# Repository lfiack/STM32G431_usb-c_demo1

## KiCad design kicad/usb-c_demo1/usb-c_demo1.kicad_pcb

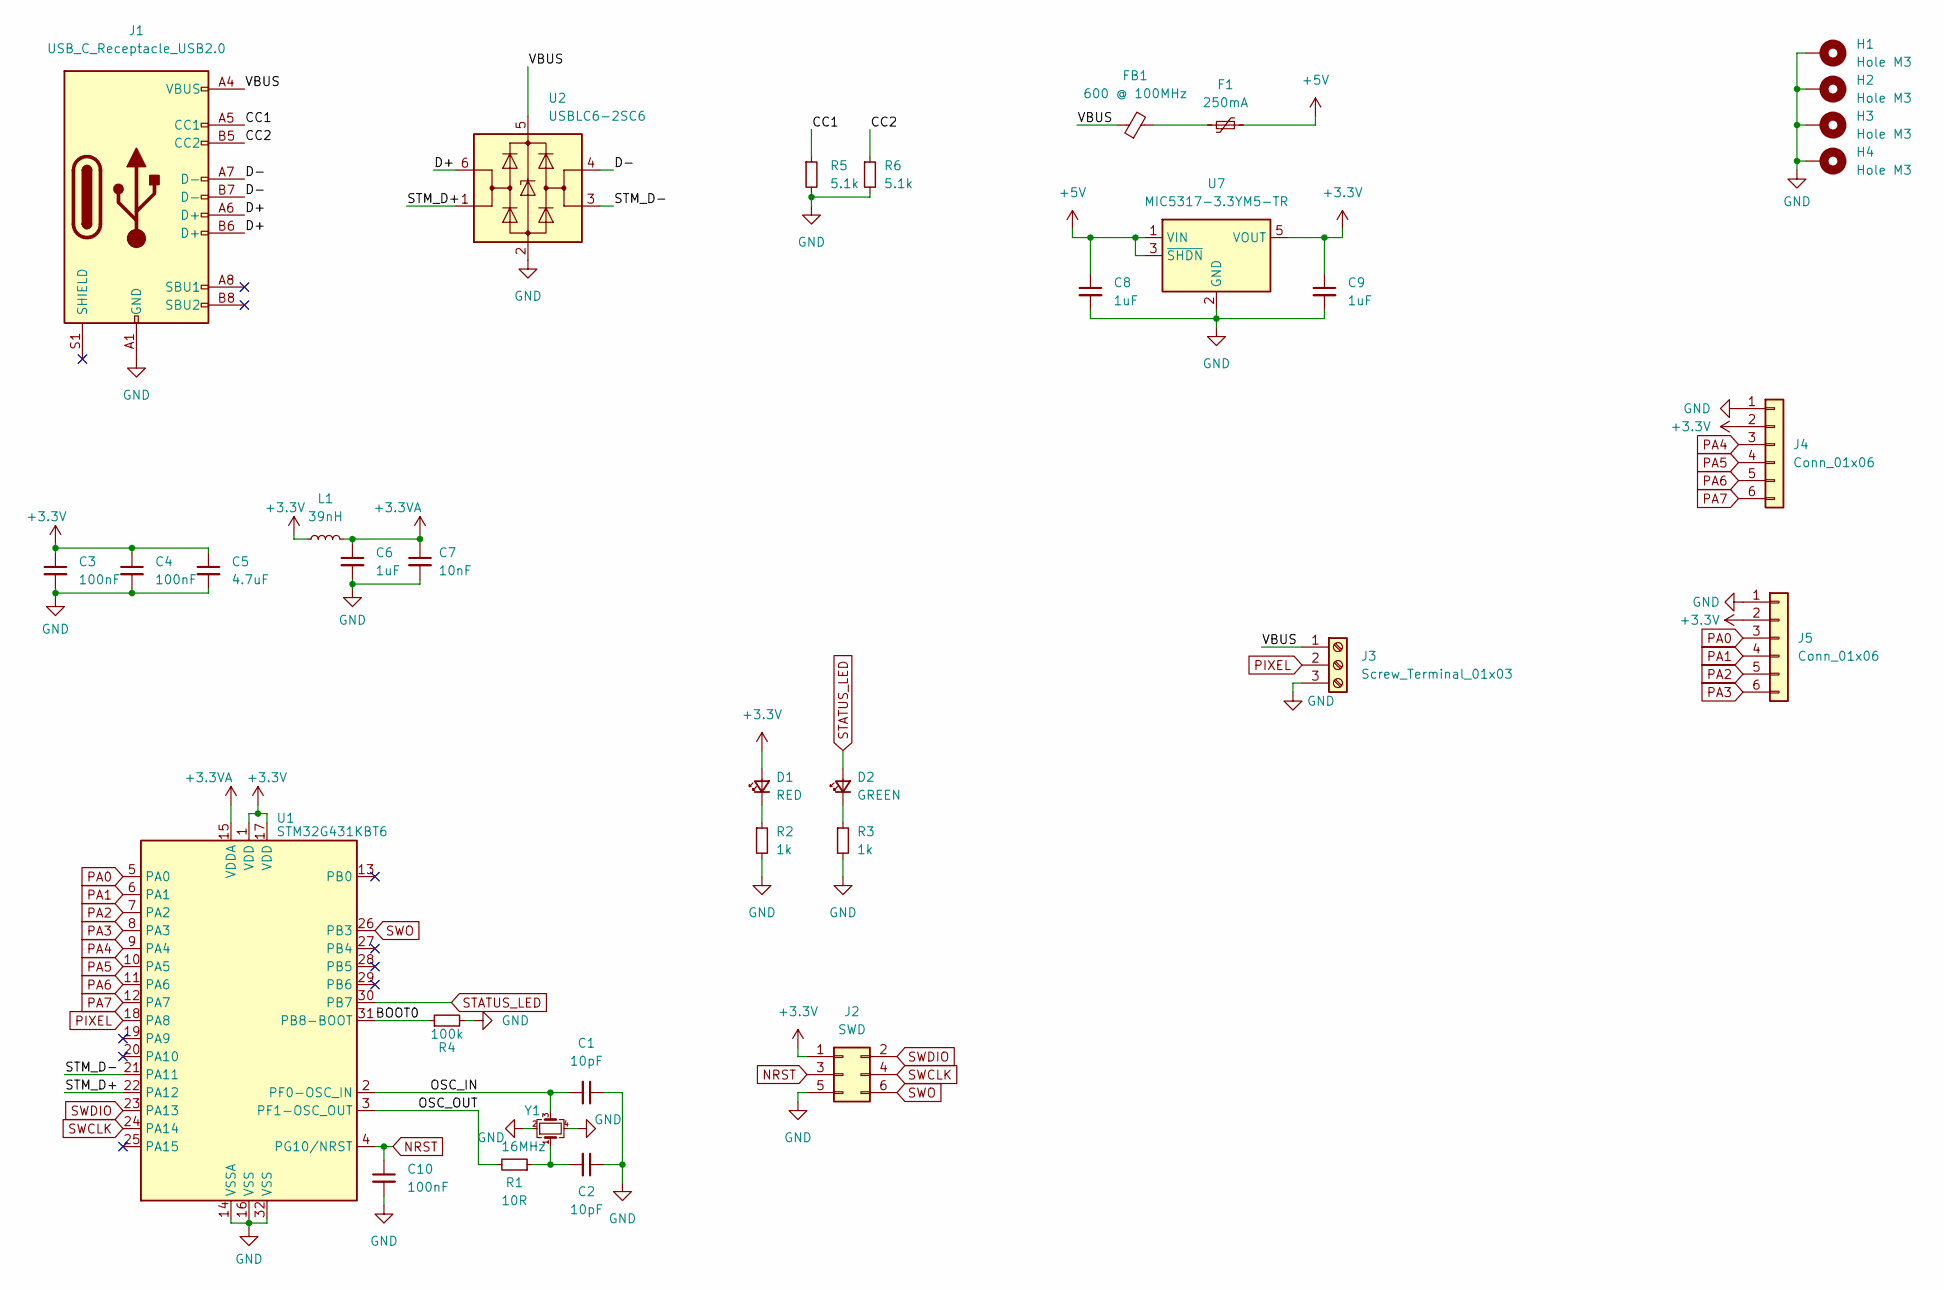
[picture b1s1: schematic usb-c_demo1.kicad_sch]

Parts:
C1, C2: 10pF; C_0603_1608Metric
C3, C4, C10: 100nF; C_0603_1608Metric
C5: 4.7uF; C_0603_1608Metric
C6, C8, C9: 1uF; C_0603_1608Metric
C7: 10nF; C_0603_1608Metric
D1: RED; LED_0603_1608Metric
D2: GREEN; LED_0603_1608Metric
F1: 250mA; Fuse_1206_3216Metric; Farnell 2834880
FB1: 600 @ 100MHz; L_0805_2012Metric_Pad1.15x1.40mm_HandSolder; Farnell 2292460
H1, H2, H3, H4: Hole M3; MountingHole_3.2mm_M3_Pad_Via
J1: USB_C_Receptacle_USB2.0; USB_C_Receptacle_HRO_TYPE-C-31-M-12
J2: SWD; solderless_swd
J3: Screw_Terminal_01x03; TerminalBlock_Phoenix_MPT-0,5-3-2.54_1x03_P2.54mm_Horizontal
J4, J5: Conn_01x06; PinHeader_1x06_P2.54mm_Vertical
L1: 39nH; L_0603_1608Metric
R1: 10R; R_0603_1608Metric
R2, R3: 1k; R_0603_1608Metric
R4: 100k; R_0603_1608Metric
R5, R6: 5.1k; R_0603_1608Metric_Pad0.98x0.95mm_HandSolder
U1: STM32G431KBT6; LQFP-32_7x7mm_P0.8mm
U2: USBLC6-2SC6; SOT-23-6
U7: MIC5317-3.3YM5-TR; SOT-23-5; Farnell 2920683
Y1: 16MHz; Crystal_SMD_EuroQuartz_MT-4Pin_3.2x2.5mm; Farnell 2853935

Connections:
+3.3VA: C6.1, C7.1, L1.2, U1.15 (VDDA)
+3V3: C3.1, C4.1, C5.1, C9.1, D1.2 (A), J2.1, J4.2, J5.2, L1.1, U1.1 (VDD), U1.17 (VDD), U7.5 (VOUT)
+5V: C8.1, F1.2, U7.1 (VIN), U7.3 (~SHDN)
/BOOT0: R4.1, U1.31 (PB8-BOOT)
/CC1: J1.A5 (CC1), R5.1
/CC2: J1.B5 (CC2), R6.1
/D+: J1.A6 (D+), J1.B6 (D+), U2.6 (I/O1)
/D-: J1.A7 (D-), J1.B7 (D-), U2.4 (I/O2)
/OSC_IN: C1.2, U1.2 (PF0-OSC_IN), Y1.3
/OSC_OUT: R1.2, U1.3 (PF1-OSC_OUT)
/STM_D+: U1.22 (PA12), U2.1 (I/O1)
/STM_D-: U1.21 (PA11), U2.3 (I/O2)
/VBUS: FB1.1, J1.A4 (VBUS), J1.A9 (VBUS), J1.B4 (VBUS), J1.B9 (VBUS), J3.1, U2.5 (VBUS)
GND: C1.1, C2.1, C3.2, C4.2, C5.2, C6.2, C7.2, C8.2, C9.2, C10.2, H1.1, H2.1, H3.1, H4.1, J1.A1 (GND), J1.A12 (GND), J1.B1 (GND), J1.B12 (GND), J2.5, J3.3, J4.1, J5.1, R2.2, R3.2, R4.2, R5.2, R6.2, U1.14 (VSSA), U1.16 (VSS), U1.32 (VSS), U2.2 (GND), U7.2 (GND), Y1.2, Y1.4
NRST: C10.1, J2.3, U1.4 (PG10/NRST)
unnamed: C2.2, R1.1, Y1.1
unnamed: D1.1 (K), R2.1
unnamed: D2.1 (K), R3.1
unnamed: F1.1, FB1.2
PA0: J5.3, U1.5 (PA0)
PA1: J5.4, U1.6 (PA1)
PA2: J5.5, U1.7 (PA2)
PA3: J5.6, U1.8 (PA3)
PA4: J4.3, U1.9 (PA4)
PA5: J4.4, U1.10 (PA5)
PA6: J4.5, U1.11 (PA6)
PA7: J4.6, U1.12 (PA7)
PIXEL: J3.2, U1.18 (PA8)
STATUS_LED: D2.2 (A), U1.30 (PB7)
SWCLK: J2.4, U1.24 (PA14)
SWDIO: J2.2, U1.23 (PA13)
SWO: J2.6, U1.26 (PB3)

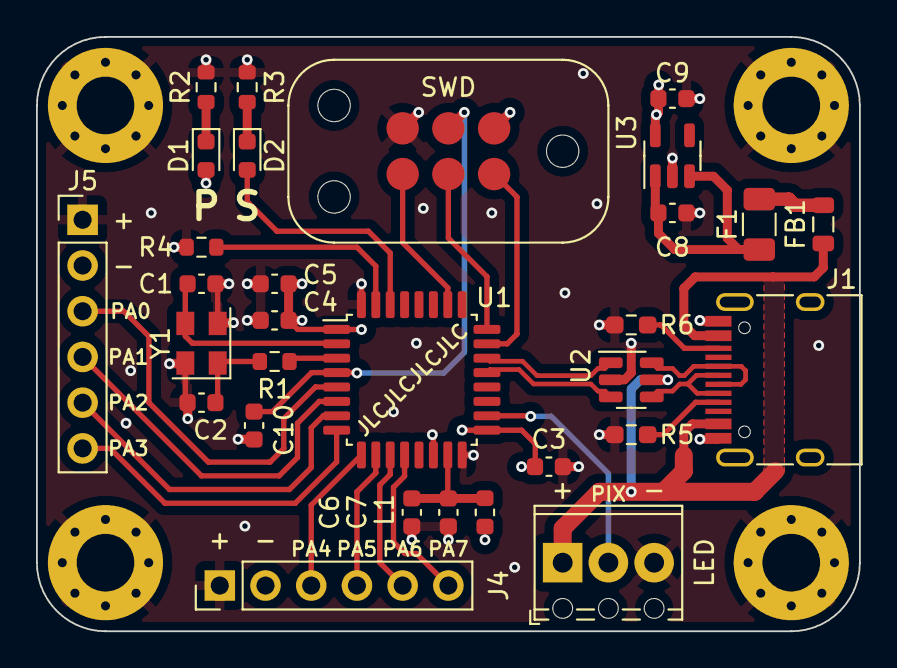
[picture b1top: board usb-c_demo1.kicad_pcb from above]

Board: 4 copper layers, 45.7 x 33.0 mm, 34 parts (0 on the bottom side), 32 nets.

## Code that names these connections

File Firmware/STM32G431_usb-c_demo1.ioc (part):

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Mcu.Name=STM32G431K(6-8-B)Tx
Mcu.Package=LQFP32
Mcu.UserName=STM32G431KBTx
PA11.Mode=Device
PA11.Signal=USB_DM
PA12.Mode=Device
PA12.Signal=USB_DP
PA13.Mode=Trace_Asynchronous_SW
PA13.Signal=SYS_JTMS-SWDIO
PA14.Mode=Trace_Asynchronous_SW
PA14.Signal=SYS_JTCK-SWCLK
PA2.Mode=Asynchronous
PA2.Signal=USART2_TX
PA3.Mode=Asynchronous
PA3.Signal=USART2_RX
PB3.Mode=Trace_Asynchronous_SW
PB3.Signal=SYS_JTDO-SWO
PB7.GPIOParameters=GPIO_Label
PB7.GPIO_Label=LED
PB7.Signal=GPIO_Output
PF0-OSC_IN.Mode=HSE-External-Oscillator
PF0-OSC_IN.Signal=RCC_OSC_IN
PF1-OSC_OUT.Mode=HSE-External-Oscillator
PF1-OSC_OUT.Signal=RCC_OSC_OUT
RCC.HSE_VALUE=16000000
RCC.SYSCLKFreq_VALUE=170000000
RCC.SYSCLKSource=RCC_SYSCLKSOURCE_PLLCLK
board=custom

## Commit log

2022-06-20 schematics
2022-06-20 cleaning libraries
2022-06-21 routing
2022-07-20 added USB-MIDI firmware for spatioport
